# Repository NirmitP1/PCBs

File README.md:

# PCBs
A collection of simple PCBs made for my TER4M0 course.<br /><br />
These projects are meant to be beginner friendly and to be used to help students develop their soldering skills.<br /><br /> 
Whether more PCBs will be added is TBD.

**Dice**:<br />
A simple dice circuit using a 555 timer and binary counter. Includes a seven segment display (common anode) to display the number.<br /><br />

**Heart**:<br />
A ring oscillator using capacitors and transistors which creates a chasing effect. The LEDs are arranged in the shape of a heart.<br /><br />

**Police lights**:<br />
An astable vibrator using capacitors and transistors. Uses blue and red LEDs to emulate police lights.<br /><br />

**Bird**:<br />
A circuit that creates a bird like sound on a button press. Uses two 555 timers, one which modulates the other to create a sweeping effect.<br /><br />

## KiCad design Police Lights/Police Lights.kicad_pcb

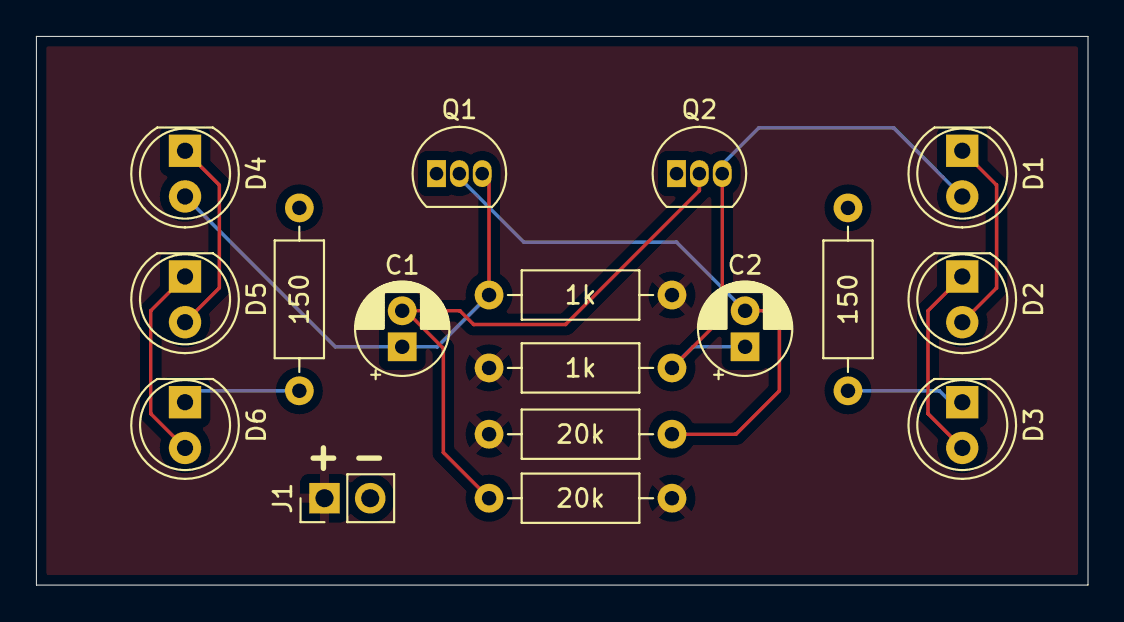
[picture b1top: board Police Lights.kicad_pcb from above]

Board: 2 copper layers, 58.4 x 30.5 mm, 17 parts (0 on the bottom side), 12 nets.

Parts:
1k, 1k#2: 1k; R_Axial_DIN0207_L6.3mm_D2.5mm_P10.16mm_Horizontal
20k, 20k#2: 20k; R_Axial_DIN0207_L6.3mm_D2.5mm_P10.16mm_Horizontal
150, 150#2: 150; R_Axial_DIN0207_L6.3mm_D2.5mm_P10.16mm_Horizontal
C1, C2: 22u; CP_Radial_D5.0mm_P2.00mm
D1, D2, D3, D4, D5, D6: LED; LED_D5.0mm
J1: Conn_01x02_Pin; PinHeader_1x02_P2.54mm_Vertical
Q1, Q2: PN2222A; TO-92_Inline

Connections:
GND: 150.2, 150#2.1, J1.2, Q1.1 (E), Q2.1 (E)
unnamed: 1k.2, C2.1, D1.2 (A), Q2.3 (C)
unnamed: D1.1 (K), D2.2 (A)
unnamed: D2.1 (K), D3.2 (A)
unnamed: 150.1, D3.1 (K)
unnamed: 1k#2.2, C1.1, D4.2 (A), Q1.3 (C)
unnamed: D4.1 (K), D5.2 (A)
unnamed: D5.1 (K), D6.2 (A)
unnamed: 150#2.2, D6.1 (K)
unnamed: 20k.2, C2.2, Q1.2 (B)
unnamed: 20k#2.2, C1.2, Q2.2 (B)
VCC: 1k.1, 1k#2.1, 20k.1, 20k#2.1, J1.1

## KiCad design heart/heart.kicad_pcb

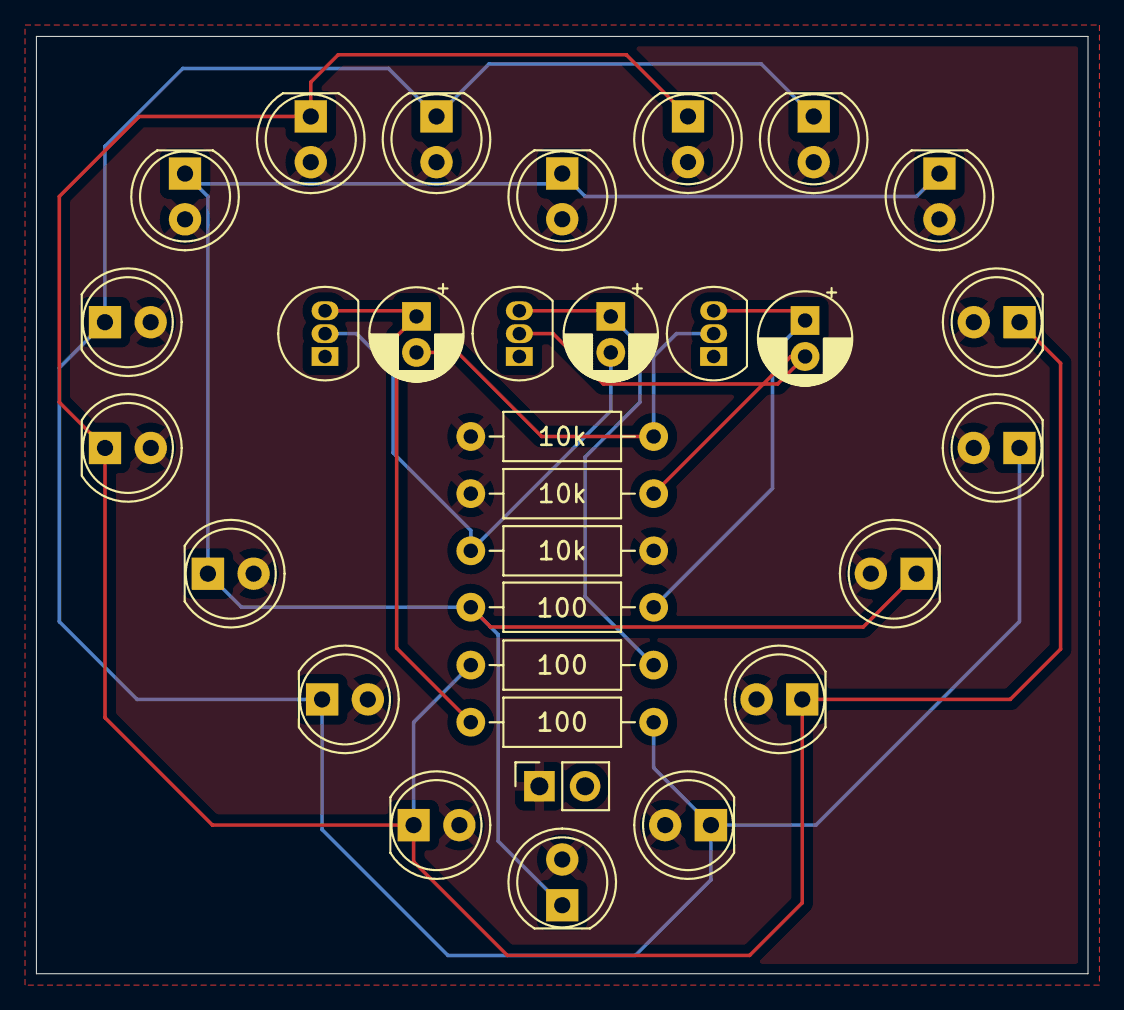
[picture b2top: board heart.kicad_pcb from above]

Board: 2 copper layers, 58.4 x 52.1 mm, 31 parts (0 on the bottom side), 11 nets.

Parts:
10k, 10k#2, 10k#3: 10k; R_Axial_DIN0207_L6.3mm_D2.5mm_P10.16mm_Horizontal
100, 100#2, 100#3: 100; R_Axial_DIN0207_L6.3mm_D2.5mm_P10.16mm_Horizontal
+: Conn_01x02_Pin; PinSocket_1x02_P2.54mm_Vertical
C1, C2, C3: 22u; CP_Radial_D5.0mm_P2.00mm
D1, D2, D3, D4, D5, D6, D7, D8, D9, D10, D11, D12, D13, D14, D15, D16, D17, D18: LED; LED_D5.0mm
Q1, Q2, Q3: PN2222A; TO-92_Inline

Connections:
GND: +.2, Q1.1 (E), Q2.1 (E), Q3.1 (E)
unnamed: 100#3.1, D1.1 (K), D2.1 (K), D3.1 (K), D4.1 (K), D5.1 (K), D6.1 (K)
unnamed: 100#2.1, D7.1 (K), D8.1 (K), D9.1 (K), D10.1 (K), D11.1 (K), D12.1 (K)
unnamed: 100.1, D13.1 (K), D14.1 (K), D15.1 (K), D16.1 (K), D17.1 (K), D18.1 (K)
unnamed: 10k#2.2, C3.2, Q1.2 (B)
unnamed: 100#3.2, C1.1, Q1.3 (C)
unnamed: 10k.2, C1.2, Q2.2 (B)
unnamed: 100#2.2, C2.1, Q2.3 (C)
unnamed: 10k#3.2, C2.2, Q3.2 (B)
unnamed: 100.2, C3.1, Q3.3 (C)
VCC: 10k.1, 10k#2.1, 10k#3.1, +.1, D1.2 (A), D2.2 (A), D3.2 (A), D4.2 (A), D5.2 (A), D6.2 (A), D7.2 (A), D8.2 (A), D9.2 (A), D10.2 (A), D11.2 (A), D12.2 (A), D13.2 (A), D14.2 (A), D15.2 (A), D16.2 (A), D17.2 (A), D18.2 (A)

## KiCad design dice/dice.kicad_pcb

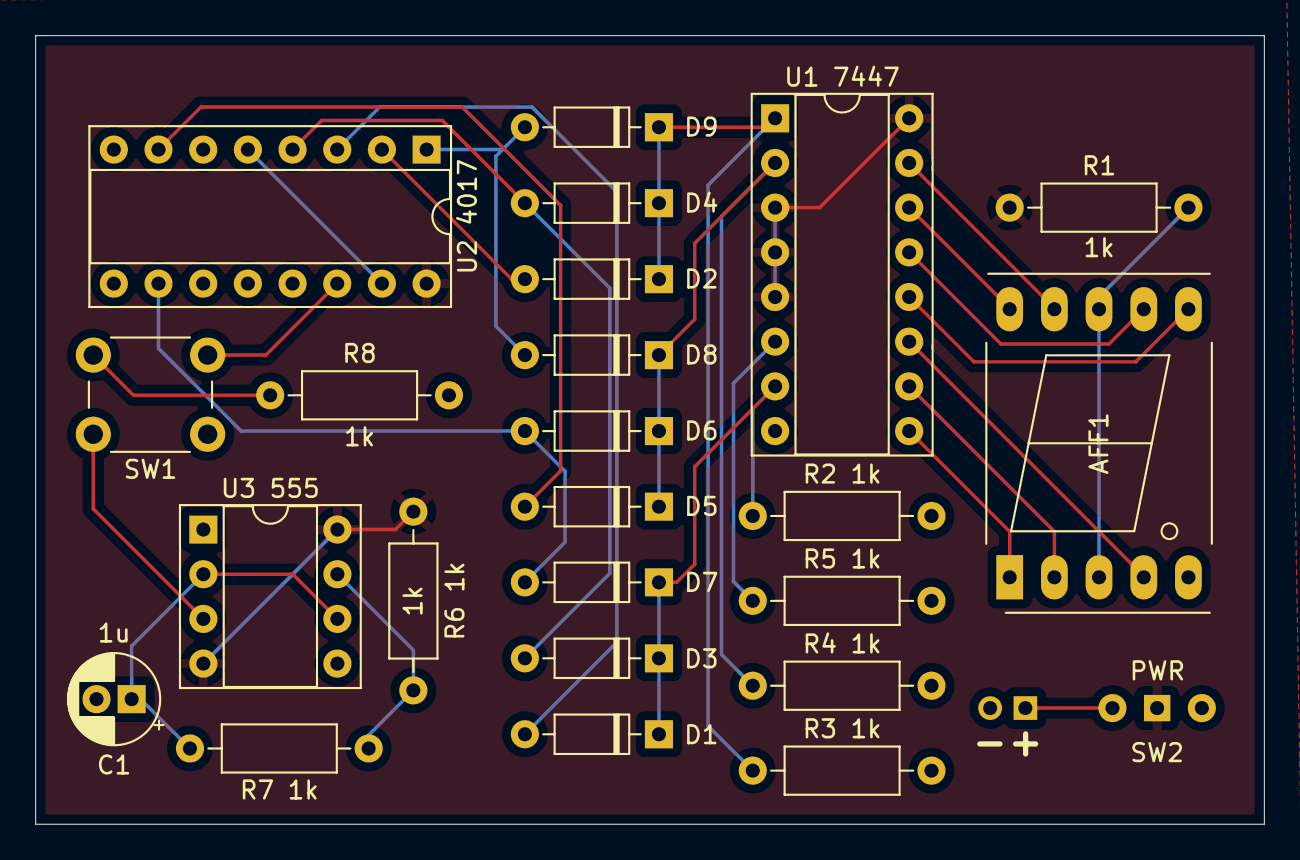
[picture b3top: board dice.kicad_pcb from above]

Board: 2 copper layers, 69.8 x 44.8 mm, 25 parts (1 on the bottom side), 27 nets.

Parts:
AFF1: LTS-6960HR; 7SegmentLED_LTS6760_LTS6780
C1: 1u; CP_Radial_D5.0mm_P2.00mm
D1, D2, D3, D4, D5, D6, D7, D8, D9: 1N4148; D_DO-35_SOD27_P7.62mm_Horizontal
J1: Conn_01x02_Pin; PinHeader_1x02_P2.00mm_Vertical
R1, R2 1k, R3 1k, R4 1k, R5 1k, R6 1k, R7 1k, R8: 1k; R_Axial_DIN0207_L6.3mm_D2.5mm_P10.16mm_Horizontal
SW1: A; SW_PUSH_6mm
SW2: SW_Wuerth_450301014042; SW_Slide-03_Wuerth-WS-SLTV_10x2.5x6.4_P2.54mm
U1 7447: 74LS47; DIP-16_W7.62mm_Socket
U2 4017: 4017; DIP-16_W7.62mm_Socket
U3 555: NE555P; DIP-8_W7.62mm_Socket

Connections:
Earth: C1.2, J1.2, R2 1k.2, R3 1k.2, R4 1k.2, R5 1k.2, R8.2, U1 7447.8 (GND), U2 4017.8 (VSS), U2 4017.13 (CKEN), U3 555.1 (GND)
unnamed: AFF1.3 (C.A.), AFF1.8 (C.A.), R1.2
unnamed: AFF1.7 (a), U1 7447.13 (a)
unnamed: AFF1.6 (b), U1 7447.12 (b)
unnamed: AFF1.4 (c), U1 7447.11 (c)
unnamed: AFF1.2 (d), U1 7447.10 (d)
unnamed: AFF1.1 (e), U1 7447.9 (e)
unnamed: AFF1.9 (f), U1 7447.15 (f)
unnamed: AFF1.10 (g), U1 7447.14 (g)
unnamed: D1.2 (A), U2 4017.3 (Q0)
unnamed: D1.1 (K), D3.1 (K), D7.1 (K), R2 1k.1, U1 7447.7 (A)
unnamed: D2.2 (A), U2 4017.2 (Q1)
unnamed: D2.1 (K), D4.1 (K), D9.1 (K), R3 1k.1, U1 7447.1 (B)
unnamed: D3.2 (A), D4.2 (A), U2 4017.4 (Q2)
unnamed: D5.2 (A), U2 4017.7 (Q3)
unnamed: D5.1 (K), D6.1 (K), D8.1 (K), R4 1k.1, U1 7447.2 (C)
unnamed: D6.2 (A), D7.2 (A), U2 4017.10 (Q4)
unnamed: D8.2 (A), D9.2 (A), U2 4017.1 (Q5)
unnamed: J1.1, SW2.2 (C)
unnamed: R8.1, SW1.4
unnamed: R5 1k.1, U1 7447.6 (D)
unnamed: SW1.3, U2 4017.14 (CLK)
unnamed: U2 4017.5 (Q6), U2 4017.15 (Reset)
unnamed: R6 1k.2, R7 1k.1, U3 555.7 (DIS)
unnamed: SW1.2, U3 555.3 (Q)
unnamed: C1.1, R7 1k.2, U3 555.2 (TR), U3 555.6 (THR)
VCC: R1.1, R6 1k.1, SW2.1 (B), U1 7447.3 (LT), U1 7447.4 (BI), U1 7447.5 (RBI), U1 7447.16 (VCC), U2 4017.16 (VDD), U3 555.4 (R), U3 555.8 (VCC)

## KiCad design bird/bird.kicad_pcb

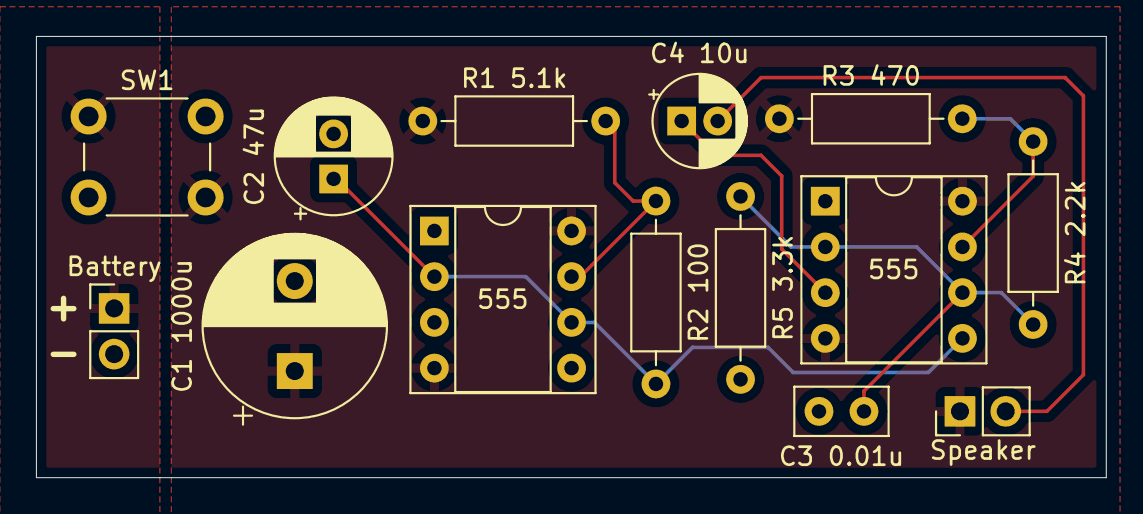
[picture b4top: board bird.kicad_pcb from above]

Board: 2 copper layers, 59.4 x 24.5 mm, 14 parts (0 on the bottom side), 9 nets.

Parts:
555, 555#2: NE555P; DIP-8_W7.62mm_Socket
Battery: Conn_01x02_Pin; PinHeader_1x02_P2.54mm_Vertical
C1 1000u: 1000u; CP_Radial_D10.0mm_P5.00mm
C2 47u: 47u; CP_Radial_D6.3mm_P2.50mm
C3 0.01u: 0.1u; C_Disc_D5.0mm_W2.5mm_P2.50mm
C4 10u: 10u; CP_Radial_D5.0mm_P2.00mm
R1 5.1k: 5.1k; R_Axial_DIN0207_L6.3mm_D2.5mm_P10.16mm_Horizontal
R2 100: 100; R_Axial_DIN0207_L6.3mm_D2.5mm_P10.16mm_Horizontal
R3 470: 470; R_Axial_DIN0207_L6.3mm_D2.5mm_P10.16mm_Horizontal
R4 2.2k: 2.2k; R_Axial_DIN0207_L6.3mm_D2.5mm_P10.16mm_Horizontal
R5 3.3k: 3.3k; R_Axial_DIN0207_L6.3mm_D2.5mm_P10.16mm_Horizontal
SW1: SW_DPST; SW_PUSH_6mm
Speaker: Speaker; PinHeader_1x02_P2.54mm_Vertical

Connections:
+BATT: Battery.1, SW1.1
GND: 555.1 (GND), 555#2.1 (GND), Battery.2, C1 1000u.2, C2 47u.2, C3 0.01u.2, R5 3.3k.2
unnamed: C4 10u.2, Speaker.2
unnamed: 555.7 (DIS), R1 5.1k.2, R2 100.1
unnamed: 555.2 (TR), 555.6 (THR), 555#2.5 (CV), C2 47u.1, R2 100.2
unnamed: 555#2.7 (DIS), R3 470.2, R4 2.2k.1
unnamed: 555#2.3 (Q), C4 10u.1
unnamed: 555#2.2 (TR), 555#2.6 (THR), C3 0.01u.1, R4 2.2k.2, R5 3.3k.1
VCC: 555.4 (R), 555.8 (VCC), 555#2.4 (R), 555#2.8 (VCC), C1 1000u.1, R1 5.1k.1, R3 470.1, SW1.4, Speaker.1
